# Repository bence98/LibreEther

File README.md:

# LibreEther
Free and open source networking devices

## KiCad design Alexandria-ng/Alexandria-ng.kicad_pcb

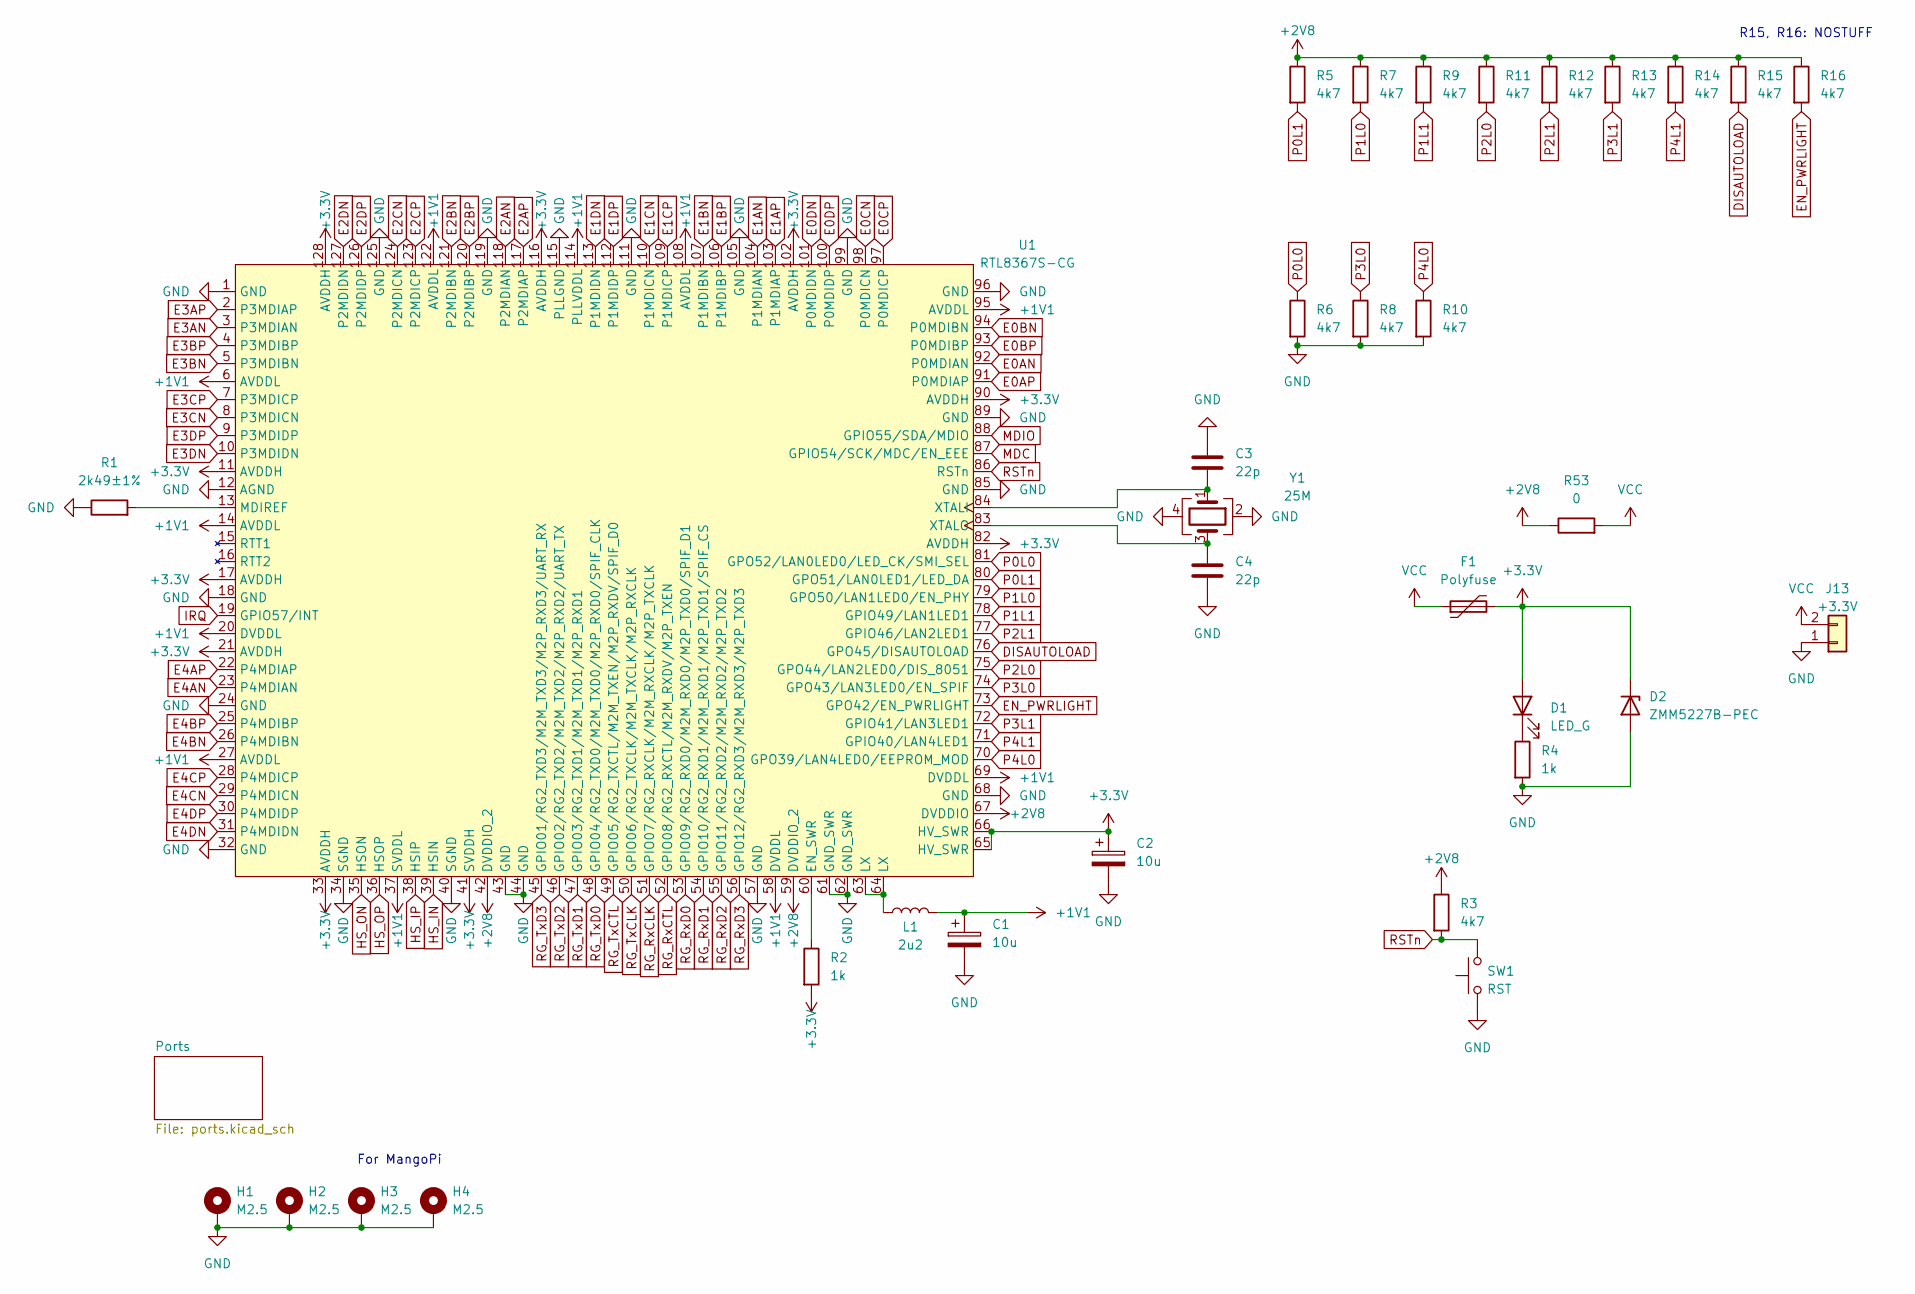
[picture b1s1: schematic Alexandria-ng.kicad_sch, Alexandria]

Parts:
C1, C2: 10u; C_1206_3216Metric_Pad1.33x1.80mm_HandSolder
C3, C4: 22p; C_0603_1608Metric_Pad1.08x0.95mm_HandSolder
D1: LED_G; LED_0603_1608Metric_Pad1.05x0.95mm_HandSolder
D2: ZMM5227B-PEC; D_MiniMELF_Handsoldering
F1: Polyfuse; Fuse_0603_1608Metric_Pad1.05x0.95mm_HandSolder
H1, H2, H3, H4: M2.5; MountingHole_2.7mm_M2.5_ISO7380_Pad
J13: +3.3V; PinHeader_1x02_P2.54mm_Vertical
L1: 2u2; L_Ferrocore_DLG-0504
R1: 2k49±1%; R_0603_1608Metric_Pad0.98x0.95mm_HandSolder
R2, R4: 1k; R_0603_1608Metric_Pad0.98x0.95mm_HandSolder
R3, R5, R6, R7, R8, R9, R10, R11, R12, R13, R14, R15, R16: 4k7; R_0603_1608Metric_Pad0.98x0.95mm_HandSolder
R53: 0; R_0603_1608Metric_Pad0.98x0.95mm_HandSolder
SW1: RST; SW_Push_1P1T_NO_6x6mm_H9.5mm
U1: RTL8367S-CG; LQFP-128_14x14mm_P0.4mm
Y1: 25M; Crystal_SMD_5032-4Pin_5.0x3.2mm

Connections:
+1V1: C1.1, L1.2, U1.6 (AVDDL), U1.14 (AVDDL), U1.20 (DVDDL), U1.27 (AVDDL), U1.37 (SVDDL), U1.58 (DVDDL), U1.69 (DVDDL), U1.95 (AVDDL), U1.108 (AVDDL), U1.114 (PLLVDDL), U1.122 (AVDDL)
+2V8: R3.1, R5.1, R7.1, R9.1, R11.1, R12.1, R13.1, R14.1, R15.1, R16.1, R53.1, U1.42 (DVDDIO_2), U1.59 (DVDDIO_2), U1.67 (DVDDIO); also elsewhere on the board
+3.3V: C2.1, D1.2 (A), D2.1 (K), F1.2, R2.2, U1.11 (AVDDH), U1.17 (AVDDH), U1.21 (AVDDH), U1.33 (AVDDH), U1.41 (SVDDH), U1.65 (HV_SWR), U1.66 (HV_SWR), U1.82 (AVDDH), U1.90 (AVDDH), U1.102 (AVDDH), U1.116 (AVDDH), U1.128 (AVDDH); also elsewhere on the board
DISAUTOLOAD: R15.2, U1.76 (GPO45/DISAUTOLOAD)
E0AN: U1.92 (P0MDIAN); also elsewhere on the board
E0AP: U1.91 (P0MDIAP); also elsewhere on the board
E0BN: U1.94 (P0MDIBN); also elsewhere on the board
E0BP: U1.93 (P0MDIBP); also elsewhere on the board
E0CN: U1.98 (P0MDICN); also elsewhere on the board
E0CP: U1.97 (P0MDICP); also elsewhere on the board
E0DN: U1.101 (P0MDIDN); also elsewhere on the board
E0DP: U1.100 (P0MDIDP); also elsewhere on the board
E1AN: U1.104 (P1MDIAN); also elsewhere on the board
E1AP: U1.103 (P1MDIAP); also elsewhere on the board
E1BN: U1.107 (P1MDIBN); also elsewhere on the board
E1BP: U1.106 (P1MDIBP); also elsewhere on the board
E1CN: U1.110 (P1MDICN); also elsewhere on the board
E1CP: U1.109 (P1MDICP); also elsewhere on the board
E1DN: U1.113 (P1MDIDN); also elsewhere on the board
E1DP: U1.112 (P1MDIDP); also elsewhere on the board
E2AN: U1.118 (P2MDIAN); also elsewhere on the board
E2AP: U1.117 (P2MDIAP); also elsewhere on the board
E2BN: U1.121 (P2MDIBN); also elsewhere on the board
E2BP: U1.120 (P2MDIBP); also elsewhere on the board
E2CN: U1.124 (P2MDICN); also elsewhere on the board
E2CP: U1.123 (P2MDICP); also elsewhere on the board
E2DN: U1.127 (P2MDIDN); also elsewhere on the board
E2DP: U1.126 (P2MDIDP); also elsewhere on the board
E3AN: U1.3 (P3MDIAN); also elsewhere on the board
E3AP: U1.2 (P3MDIAP); also elsewhere on the board
E3BN: U1.5 (P3MDIBN); also elsewhere on the board
E3BP: U1.4 (P3MDIBP); also elsewhere on the board
E3CN: U1.8 (P3MDICN); also elsewhere on the board
E3CP: U1.7 (P3MDICP); also elsewhere on the board
E3DN: U1.10 (P3MDIDN); also elsewhere on the board
E3DP: U1.9 (P3MDIDP); also elsewhere on the board
E4AN: U1.23 (P4MDIAN); also elsewhere on the board
E4AP: U1.22 (P4MDIAP); also elsewhere on the board
E4BN: U1.26 (P4MDIBN); also elsewhere on the board
E4BP: U1.25 (P4MDIBP); also elsewhere on the board
E4CN: U1.29 (P4MDICN); also elsewhere on the board
E4CP: U1.28 (P4MDICP); also elsewhere on the board
E4DN: U1.31 (P4MDIDN); also elsewhere on the board
E4DP: U1.30 (P4MDIDP); also elsewhere on the board
EN_PWRLIGHT: R16.2, U1.73 (GPO42/EN_PWRLIGHT)
GND: C1.2, C2.2, C3.1, C4.2, D2.2 (A), H1.1, H2.1, H3.1, H4.1, J13.1, R1.1, R4.2, R6.2, R8.2, R10.2, SW1.1, U1.1 (GND), U1.12 (AGND), U1.18 (GND), U1.24 (GND), U1.32 (GND), U1.34 (SGND), U1.40 (SGND), U1.43 (GND), U1.44 (GND), U1.57 (GND), U1.61 (GND_SWR), U1.62 (GND_SWR), U1.68 (GND), U1.85 (GND), U1.89 (GND), U1.96 (GND), U1.99 (GND), U1.105 (GND), U1.111 (GND), U1.115 (PLLGND), U1.119 (GND), U1.125 (GND), Y1.2, Y1.4; also elsewhere on the board
HS_IN: U1.39 (HSIN); also elsewhere on the board
HS_IP: U1.38 (HSIP); also elsewhere on the board
HS_ON: U1.35 (HSON); also elsewhere on the board
HS_OP: U1.36 (HSOP); also elsewhere on the board
IRQ: U1.19 (GPIO57/INT); also elsewhere on the board
MDC: U1.87 (GPIO54/SCK/MDC/EN_EEE); also elsewhere on the board
MDIO: U1.88 (GPIO55/SDA/MDIO); also elsewhere on the board
unnamed: D1.1 (K), R4.1
unnamed: L1.1, U1.63 (LX), U1.64 (LX)
unnamed: R2.1, U1.60 (EN_SWR)
unnamed: R1.2, U1.13 (MDIREF)
unnamed: C3.2, U1.84 (XTALI), Y1.1
unnamed: C4.1, U1.83 (XTALO), Y1.3
P0L0: R6.1, U1.81 (GPO52/LAN0LED0/LED_CK/SMI_SEL); also elsewhere on the board
P0L1: R5.2, U1.80 (GPO51/LAN0LED1/LED_DA); also elsewhere on the board
P1L0: R7.2, U1.79 (GPO50/LAN1LED0/EN_PHY); also elsewhere on the board
P1L1: R9.2, U1.78 (GPIO49/LAN1LED1); also elsewhere on the board
P2L0: R11.2, U1.75 (GPO44/LAN2LED0/DIS_8051); also elsewhere on the board
P2L1: R12.2, U1.77 (GPIO46/LAN2LED1); also elsewhere on the board
P3L0: R8.1, U1.74 (GPO43/LAN3LED0/EN_SPIF); also elsewhere on the board
P3L1: R13.2, U1.72 (GPIO41/LAN3LED1); also elsewhere on the board
P4L0: R10.1, U1.70 (GPO39/LAN4LED0/EEPROM_MOD); also elsewhere on the board
P4L1: R14.2, U1.71 (GPIO40/LAN4LED1); also elsewhere on the board
RG_RxCLK: U1.51 (GPIO07/RG2_RXCLK/M2M_RXCLK/M2P_TXCLK); also elsewhere on the board
RG_RxCTL: U1.52 (GPIO08/RG2_RXCTL/M2M_RXDV/M2P_TXEN); also elsewhere on the board
RG_RxD0: U1.53 (GPIO09/RG2_RXD0/M2M_RXD0/M2P_TXD0/SPIF_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); also elsewhere on the board
RG_RxD1: U1.54 (GPIO10/RG2_RXD1/M2M_RXD1/M2P_TXD1/SPIF_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); also elsewhere on the board
RG_RxD2: U1.55 (GPIO11/RG2_RXD2/M2M_RXD2/M2P_TXD2); also elsewhere on the board
RG_RxD3: U1.56 (GPIO12/RG2_RXD3/M2M_RXD3/M2P_TXD3); also elsewhere on the board
RG_TxCLK: U1.50 (GPIO06/RG2_TXCLK/M2M_TXCLK/M2P_RXCLK); also elsewhere on the board
RG_TxCTL: U1.49 (GPIO05/RG2_TXCTL/M2M_TXEN/M2P_RXDV/SPIF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); also elsewhere on the board
RG_TxD0: U1.48 (GPIO04/RG2_TXD0/M2M_TXD0/M2P_RXD0/SPIF_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); also elsewhere on the board
RG_TxD1: U1.47 (GPIO03/RG2_TXD1/M2M_TXD1/M2P_RXD1); also elsewhere on the board
RG_TxD2: U1.46 (GPIO02/RG2_TXD2/M2M_TXD2/M2P_RXD2/UART_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); also elsewhere on the board
RG_TxD3: U1.45 (GPIO01/RG2_TXD3/M2M_TXD3/M2P_RXD3/UART_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); also elsewhere on the board
RSTn: R3.2, SW1.2, U1.86 (RSTn)
VCC: F1.1, J13.2, R53.2

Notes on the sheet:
For MangoPi
R15, R16: NOSTUFF

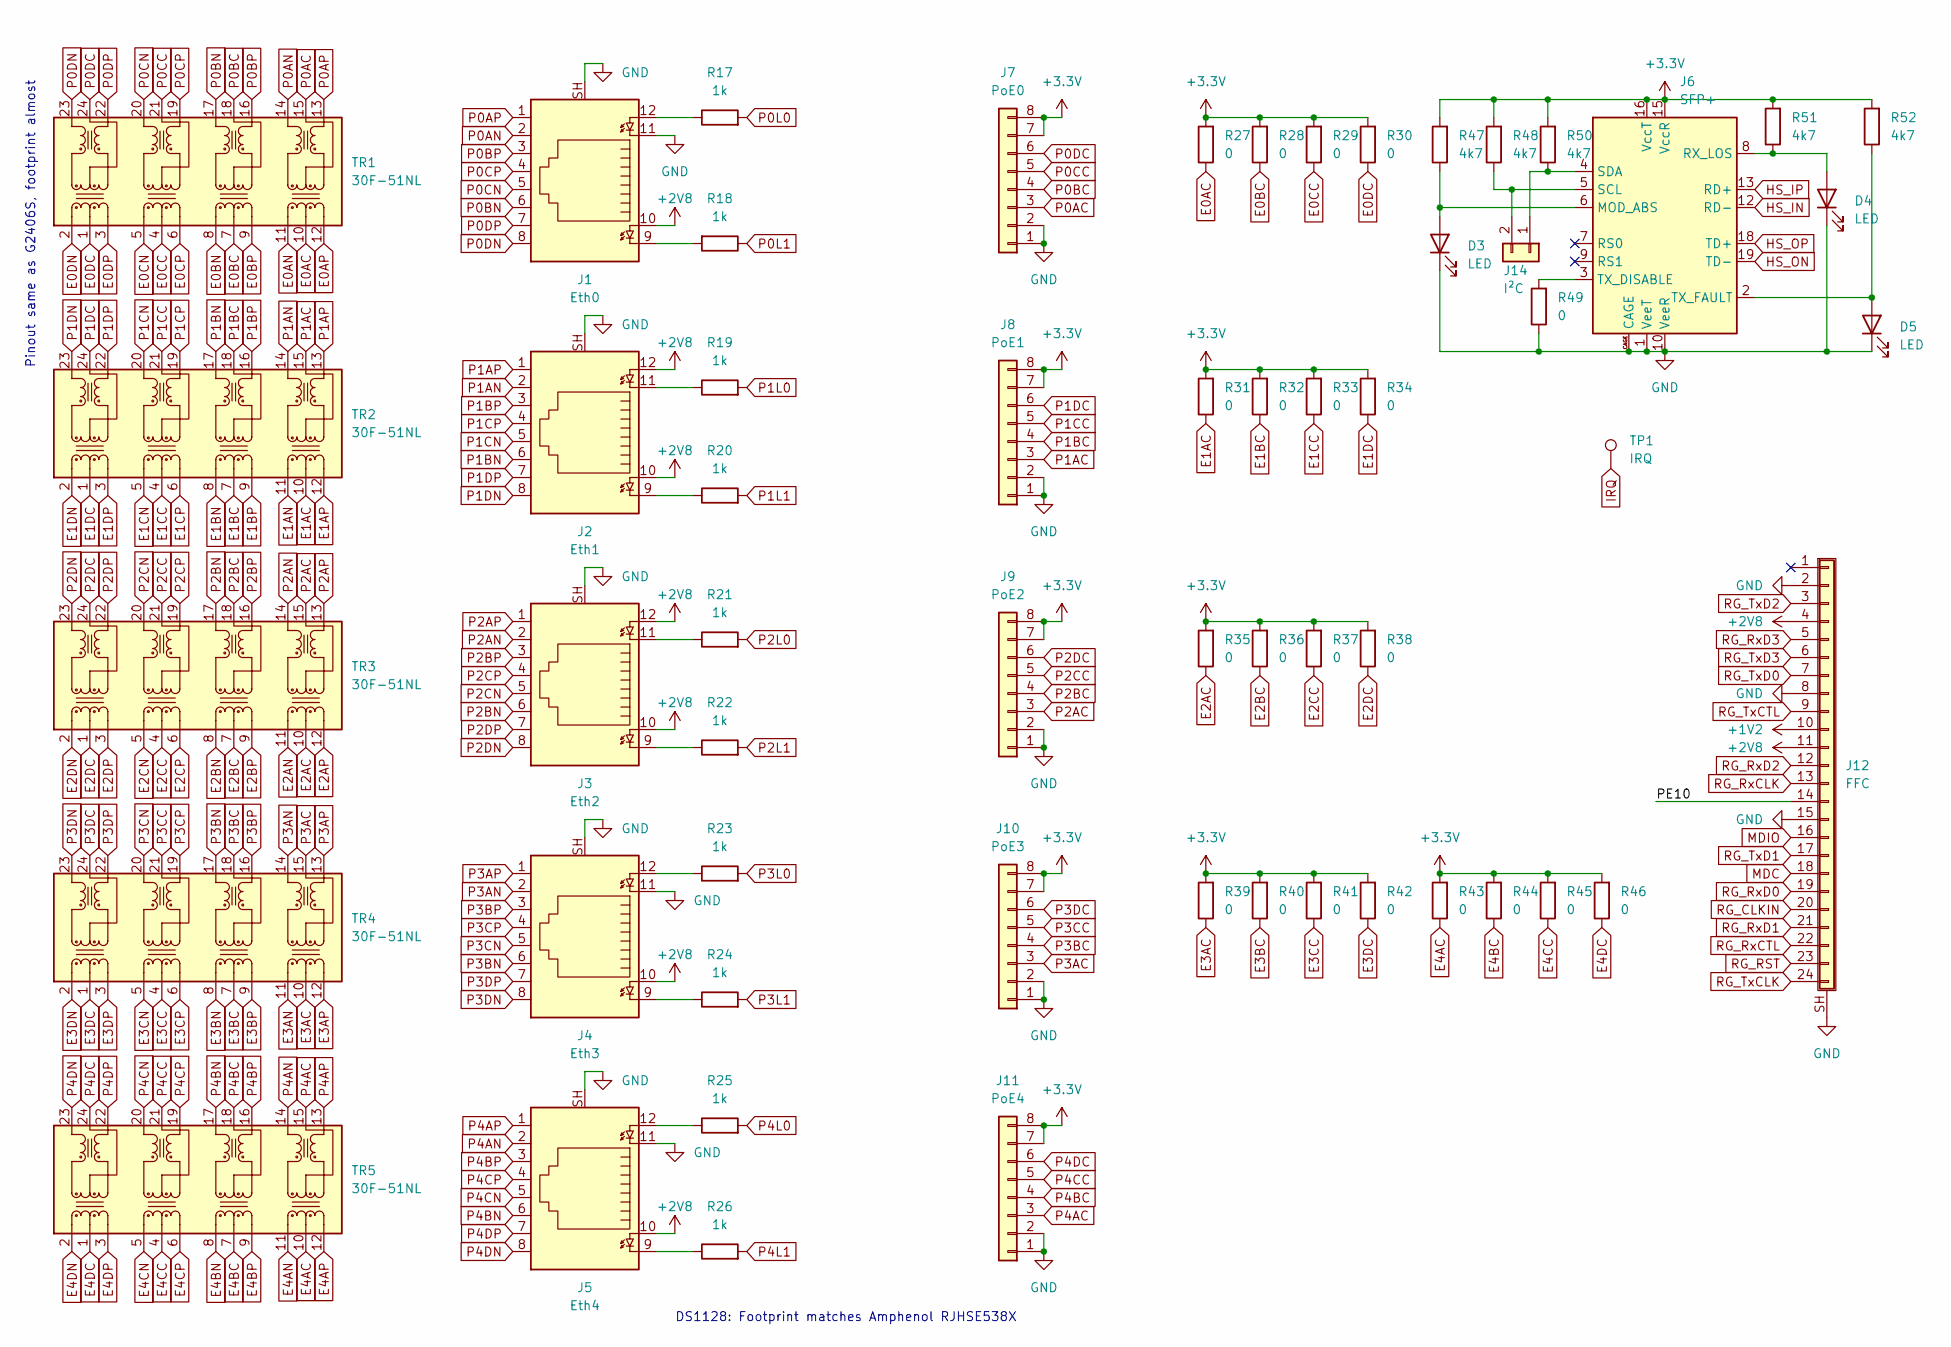
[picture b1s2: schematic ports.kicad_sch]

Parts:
D3, D4, D5: LED; LED_0603_1608Metric_Pad1.05x0.95mm_HandSolder
J1: Eth0; RJ45_Amphenol_RJHSE538X
J2: Eth1; RJ45_Amphenol_RJHSE538X
J3: Eth2; RJ45_Amphenol_RJHSE538X
J4: Eth3; RJ45_Amphenol_RJHSE538X
J5: Eth4; RJ45_Amphenol_RJHSE538X
J6: SFP+; Connector_SFP_and_Cage
J7: PoE0; PinHeader_1x08_P2.54mm_Vertical
J8: PoE1; PinHeader_1x08_P2.54mm_Vertical
J9: PoE2; PinHeader_1x08_P2.54mm_Vertical
J10: PoE3; PinHeader_1x08_P2.54mm_Vertical
J11: PoE4; PinHeader_1x08_P2.54mm_Vertical
J12: FFC; Jushuo_AFC07-S24FCA-00_1x24-1MP_P0.50_Horizontal
J14: I²C; PinHeader_1x02_P2.54mm_Vertical
R17, R18, R19, R20, R21, R22, R23, R24, R25, R26: 1k; R_0603_1608Metric_Pad0.98x0.95mm_HandSolder
R27, R28, R29, R30, R31, R32, R33, R34, R35, R36, R37, R38, R39, R40, R41, R42, R43, R44, R45, R46, R49: 0; R_0603_1608Metric_Pad0.98x0.95mm_HandSolder
R47, R48, R50, R51, R52: 4k7; R_0603_1608Metric_Pad0.98x0.95mm_HandSolder
TP1: IRQ; TestPoint_Pad_D1.0mm
TR1, TR2, TR3, TR4, TR5: 30F-51NL; Transformer_Ethernet_YDS_30F-51NL_SO-24_7.1x15.1mm

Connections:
+1V2: J12.10
+2V8: J1.10, J2.10, J2.12, J3.10, J3.12, J4.10, J5.10, J12.4, J12.11; also elsewhere on the board
+3.3V: J6.15 (VccR), J6.16 (VccT), J7.7, J7.8, J8.7, J8.8, J9.7, J9.8, J10.7, J10.8, J11.7, J11.8, R27.2, R28.2, R29.2, R30.2, R31.2, R32.2, R33.2, R34.2, R35.2, R36.2, R37.2, R38.2, R39.2, R40.2, R41.2, R42.2, R43.2, R44.2, R45.2, R46.2, R47.2, R48.2, R50.2, R51.2, R52.2; also elsewhere on the board
/Ports/PE10: J12.14
E0AC: R27.1, TR1.10 (CT)
E0AN: TR1.11 (TD4+); also elsewhere on the board
E0AP: TR1.12 (TD4-); also elsewhere on the board
E0BC: R28.1, TR1.7 (CT)
E0BN: TR1.8 (TD3+); also elsewhere on the board
E0BP: TR1.9 (TD3-); also elsewhere on the board
E0CC: R29.1, TR1.4 (CT)
E0CN: TR1.5 (TD2+); also elsewhere on the board
E0CP: TR1.6 (TD2-); also elsewhere on the board
E0DC: R30.1, TR1.1 (CT)
E0DN: TR1.2 (TD1+); also elsewhere on the board
E0DP: TR1.3 (TD1-); also elsewhere on the board
E1AC: R31.1, TR2.10 (CT)
E1AN: TR2.11 (TD4+); also elsewhere on the board
E1AP: TR2.12 (TD4-); also elsewhere on the board
E1BC: R32.1, TR2.7 (CT)
E1BN: TR2.8 (TD3+); also elsewhere on the board
E1BP: TR2.9 (TD3-); also elsewhere on the board
E1CC: R33.1, TR2.4 (CT)
E1CN: TR2.5 (TD2+); also elsewhere on the board
E1CP: TR2.6 (TD2-); also elsewhere on the board
E1DC: R34.1, TR2.1 (CT)
E1DN: TR2.2 (TD1+); also elsewhere on the board
E1DP: TR2.3 (TD1-); also elsewhere on the board
E2AC: R35.1, TR3.10 (CT)
E2AN: TR3.11 (TD4+); also elsewhere on the board
E2AP: TR3.12 (TD4-); also elsewhere on the board
E2BC: R36.1, TR3.7 (CT)
E2BN: TR3.8 (TD3+); also elsewhere on the board
E2BP: TR3.9 (TD3-); also elsewhere on the board
E2CC: R37.1, TR3.4 (CT)
E2CN: TR3.5 (TD2+); also elsewhere on the board
E2CP: TR3.6 (TD2-); also elsewhere on the board
E2DC: R38.1, TR3.1 (CT)
E2DN: TR3.2 (TD1+); also elsewhere on the board
E2DP: TR3.3 (TD1-); also elsewhere on the board
E3AC: R39.1, TR4.10 (CT)
E3AN: TR4.11 (TD4+); also elsewhere on the board
E3AP: TR4.12 (TD4-); also elsewhere on the board
E3BC: R40.1, TR4.7 (CT)
E3BN: TR4.8 (TD3+); also elsewhere on the board
E3BP: TR4.9 (TD3-); also elsewhere on the board
E3CC: R41.1, TR4.4 (CT)
E3CN: TR4.5 (TD2+); also elsewhere on the board
E3CP: TR4.6 (TD2-); also elsewhere on the board
E3DC: R42.1, TR4.1 (CT)
E3DN: TR4.2 (TD1+); also elsewhere on the board
E3DP: TR4.3 (TD1-); also elsewhere on the board
E4AC: R43.1, TR5.10 (CT)
E4AN: TR5.11 (TD4+); also elsewhere on the board
E4AP: TR5.12 (TD4-); also elsewhere on the board
E4BC: R44.1, TR5.7 (CT)
E4BN: TR5.8 (TD3+); also elsewhere on the board
E4BP: TR5.9 (TD3-); also elsewhere on the board
E4CC: R45.1, TR5.4 (CT)
E4CN: TR5.5 (TD2+); also elsewhere on the board
E4CP: TR5.6 (TD2-); also elsewhere on the board
E4DC: R46.1, TR5.1 (CT)
E4DN: TR5.2 (TD1+); also elsewhere on the board
E4DP: TR5.3 (TD1-); also elsewhere on the board
GND: D3.1 (K), D4.1 (K), D5.1 (K), J1.11, J1.SH, J2.SH, J3.SH, J4.11, J4.SH, J5.11, J5.SH, J6.1 (VeeT), J6.10 (VeeR), J6.11 (VeeR), J6.14 (VeeR), J6.17 (VeeT), J6.20 (VeeT), J6.CAGE, J7.1, J7.2, J8.1, J8.2, J9.1, J9.2, J10.1, J10.2, J11.1, J11.2, J12.2, J12.8, J12.15, J12.SH (Shield), R49.1; also elsewhere on the board
HS_IN: J6.12 (RD-); also elsewhere on the board
HS_IP: J6.13 (RD+); also elsewhere on the board
HS_ON: J6.19 (TD-); also elsewhere on the board
HS_OP: J6.18 (TD+); also elsewhere on the board
IRQ: TP1.1; also elsewhere on the board
MDC: J12.18; also elsewhere on the board
MDIO: J12.16; also elsewhere on the board
unnamed: D3.2 (A), J6.6 (MOD_ABS), R47.1
unnamed: D4.2 (A), J6.8 (RX_LOS), R51.1
unnamed: D5.2 (A), J6.2 (TX_FAULT), R52.1
unnamed: J1.9, R18.2
unnamed: J1.12, R17.1
unnamed: J2.9, R20.1
unnamed: J2.11, R19.1
unnamed: J3.9, R22.1
unnamed: J3.11, R21.1
unnamed: J4.9, R24.1
unnamed: J4.12, R23.1
unnamed: J5.9, R26.1
unnamed: J5.12, R25.1
unnamed: J6.3 (TX_DISABLE), R49.2
unnamed: J6.4 (SDA), J14.1, R50.1
unnamed: J6.5 (SCL), J14.2, R48.1
P0AC: J7.3, TR1.15 (CT)
P0AN: J1.2, TR1.14 (MX4+)
P0AP: J1.1, TR1.13 (MX4-)
P0BC: J7.4, TR1.18 (CT)
P0BN: J1.6, TR1.17 (MX3+)
P0BP: J1.3, TR1.16 (MX3-)
P0CC: J7.5, TR1.21 (CT)
P0CN: J1.5, TR1.20 (MX2+)
P0CP: J1.4, TR1.19 (MX2-)
P0DC: J7.6, TR1.24 (CT)
P0DN: J1.8, TR1.23 (MX1+)
P0DP: J1.7, TR1.22 (MX1-)
P0L0: R17.2; also elsewhere on the board
P0L1: R18.1; also elsewhere on the board
P1AC: J8.3, TR2.15 (CT)
P1AN: J2.2, TR2.14 (MX4+)
P1AP: J2.1, TR2.13 (MX4-)
P1BC: J8.4, TR2.18 (CT)
P1BN: J2.6, TR2.17 (MX3+)
P1BP: J2.3, TR2.16 (MX3-)
P1CC: J8.5, TR2.21 (CT)
P1CN: J2.5, TR2.20 (MX2+)
P1CP: J2.4, TR2.19 (MX2-)
P1DC: J8.6, TR2.24 (CT)
P1DN: J2.8, TR2.23 (MX1+)
P1DP: J2.7, TR2.22 (MX1-)
P1L0: R19.2; also elsewhere on the board
P1L1: R20.2; also elsewhere on the board
P2AC: J9.3, TR3.15 (CT)
P2AN: J3.2, TR3.14 (MX4+)
P2AP: J3.1, TR3.13 (MX4-)
P2BC: J9.4, TR3.18 (CT)
P2BN: J3.6, TR3.17 (MX3+)
P2BP: J3.3, TR3.16 (MX3-)
P2CC: J9.5, TR3.21 (CT)
P2CN: J3.5, TR3.20 (MX2+)
P2CP: J3.4, TR3.19 (MX2-)
P2DC: J9.6, TR3.24 (CT)
P2DN: J3.8, TR3.23 (MX1+)
P2DP: J3.7, TR3.22 (MX1-)
P2L0: R21.2; also elsewhere on the board
P2L1: R22.2; also elsewhere on the board
P3AC: J10.3, TR4.15 (CT)
P3AN: J4.2, TR4.14 (MX4+)
P3AP: J4.1, TR4.13 (MX4-)
P3BC: J10.4, TR4.18 (CT)
P3BN: J4.6, TR4.17 (MX3+)
P3BP: J4.3, TR4.16 (MX3-)
P3CC: J10.5, TR4.21 (CT)
P3CN: J4.5, TR4.20 (MX2+)
P3CP: J4.4, TR4.19 (MX2-)
P3DC: J10.6, TR4.24 (CT)
P3DN: J4.8, TR4.23 (MX1+)
P3DP: J4.7, TR4.22 (MX1-)
P3L0: R23.2; also elsewhere on the board
P3L1: R24.2; also elsewhere on the board
P4AC: J11.3, TR5.15 (CT)
P4AN: J5.2, TR5.14 (MX4+)
P4AP: J5.1, TR5.13 (MX4-)
P4BC: J11.4, TR5.18 (CT)
P4BN: J5.6, TR5.17 (MX3+)
P4BP: J5.3, TR5.16 (MX3-)
P4CC: J11.5, TR5.21 (CT)
P4CN: J5.5, TR5.20 (MX2+)
P4CP: J5.4, TR5.19 (MX2-)
P4DC: J11.6, TR5.24 (CT)
P4DN: J5.8, TR5.23 (MX1+)
P4DP: J5.7, TR5.22 (MX1-)
P4L0: R25.2; also elsewhere on the board
P4L1: R26.2; also elsewhere on the board
RG_CLKIN: J12.20
RG_RST: J12.23
RG_RxCLK: J12.13; also elsewhere on the board
RG_RxCTL: J12.22; also elsewhere on the board
RG_RxD0: J12.19; also elsewhere on the board
RG_RxD1: J12.21; also elsewhere on the board
RG_RxD2: J12.12; also elsewhere on the board
RG_RxD3: J12.5; also elsewhere on the board
RG_TxCLK: J12.24; also elsewhere on the board
RG_TxCTL: J12.9; also elsewhere on the board
RG_TxD0: J12.7; also elsewhere on the board
RG_TxD1: J12.17; also elsewhere on the board
RG_TxD2: J12.3; also elsewhere on the board
RG_TxD3: J12.6; also elsewhere on the board

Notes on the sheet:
DS1128: Footprint matches Amphenol RJHSE538X
Pinout same as G2406S, footprint almost

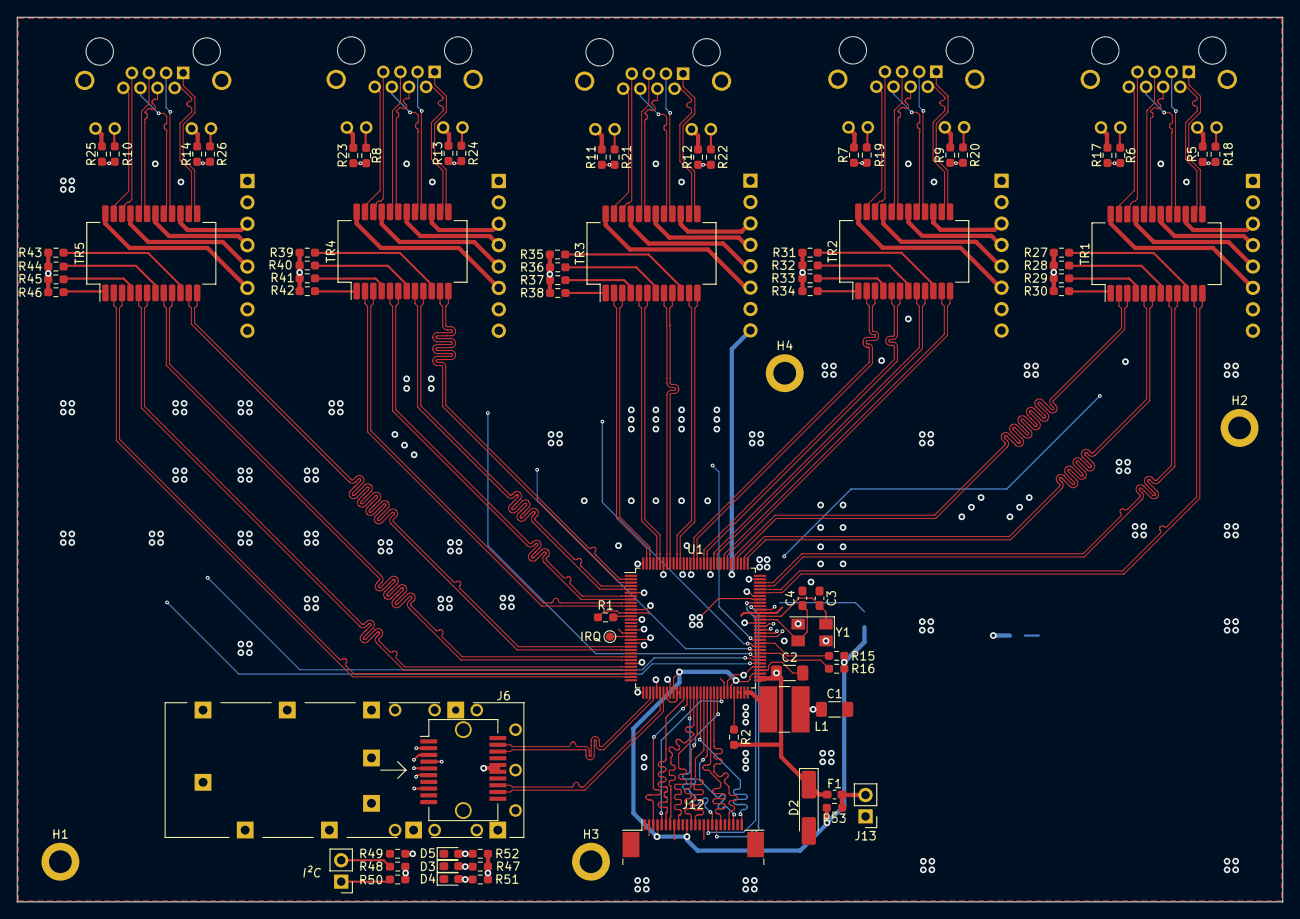
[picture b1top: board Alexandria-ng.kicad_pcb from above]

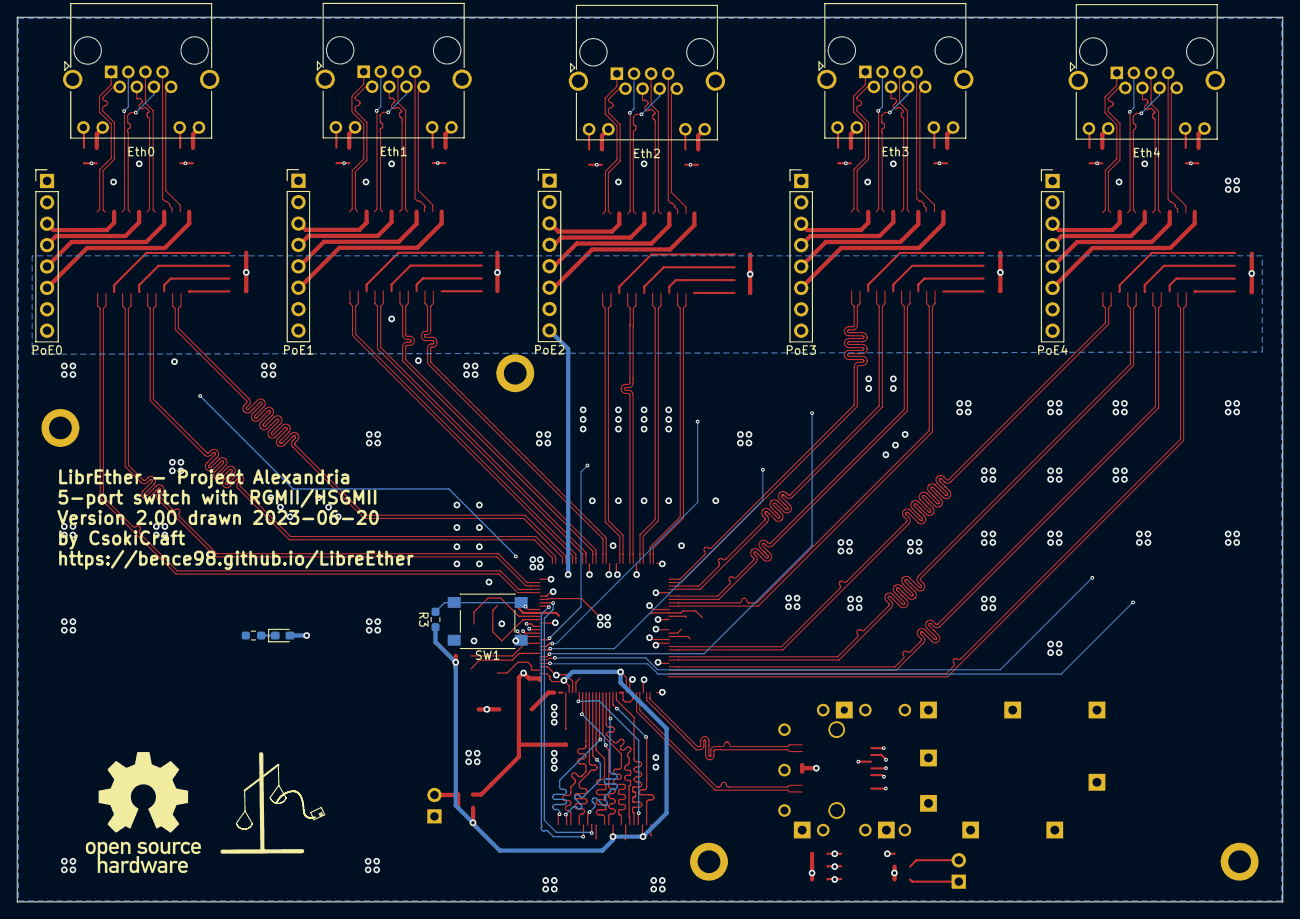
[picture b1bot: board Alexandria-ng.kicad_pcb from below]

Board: 4 copper layers, 150.2 x 105.0 mm, 91 parts (14 on the bottom side), 179 nets.

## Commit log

2022-06-27 Set theme jekyll-theme-architect
2022-06-28 Add Alexandria files
2022-06-28 Add Alexandria link
2022-07-06 Update Alexandria: add protective Zener and polyfuse, power on LED and corner screw holes
    Suggested by @kissadamfkut
2022-07-27 Replace G2401S with G2406S as it is now `Discontinued` on LCSC
2023-03-03 Alexandria re-drawn in KiCad
2023-03-15 Update to KiCad 7.0, add footprint to RJ45 jacks
2023-05-11 Annotate & assign footprints
2023-05-12 Re-do VCC and RST, add VCC connector
2023-05-12 Add IRQ test point & SFP I2C header
2023-05-18 Beginning PCB design * added JLC 3313 stackup * laid out component groups by function * started routing low speed lines
2023-05-19 Re-doing Ethernet magnetics area
2023-05-19 Fixing some DRC errors
2023-05-21 Tuning Ethernet MDI diff pairs at the RJ45 jack
2023-05-21 Routing SGMII to the SFP cage
2023-05-21 Switch DVDDIO pins to +2.8V
2023-05-25 Balance vias on Ethernet jack, unroute RGMII (way too much skew)
2023-05-25 Set via size to minimum preferred for JLCPCB
2023-05-25 Finally routed RGMII with length matching
2023-05-25 Change via sizes to new minimum
2023-05-26 Finally routed Ethernet pairs, added power rail fills under the IC
2023-05-29 Power routing
2023-06-03 More power routing
2023-06-03 GND improvements
2023-06-06 DRC fixes
2023-06-10 Finally routed all nets
2023-06-20 Added GND vias
2023-06-20 Back silkscreen
2023-06-20 Adding LibreEther logo (originally drawn 2022-06-27)
2023-06-21 More silkscreen work
2023-06-21 Re-fill zones, fix some DRC warnings
2025-05-08 Update project files
2025-05-25 pcb: Add mounting holes, fix routing of LEDs around it
2025-05-25 Update project to KiCAD 9.0.1
    No content changes, hopefully
2025-05-25 pcb: Change via sizes
2025-05-25 sch: Add mounting holes
2025-05-25 Raise min. via size to .45
    Even though JLC's min. preferred is .35, they say they can't manufacture
    it without adding 36.14 EUR for 4-wire Kelvin testing...
2025-05-25 pcb: Update to KiCAD 9
    No content changes, hopefully
2025-05-25 pcb: Unfill zones
2025-05-25 pcb: Move vias to resolve clearance issues
2025-05-26 pcb: Resolve DRC errors around Eth jacks
